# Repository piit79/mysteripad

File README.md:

# Mysteripad

#### WARNING: This project is a work in progress and hasn't been validated yet.

Mysteripad is a through-hole numeric keyboard (or "numpad") matching the form 
factor of the [Mysterium keyboard]((https://github.com/piit79/mysterium)) 
([original](https://github.com/coseyfannitutti/mysterium)), much like the 
[Discipad](https://github.com/piit79/discipad) 
([original](https://github.com/coseyfannitutti/discipad)) matches the 
[Discipline](https://github.com/piit79/discipline) 
([original](https://github.com/coseyfannitutti/discipline)).

Mysteripad was inspired by (but is not based on) the [Discipad](https://github.com/coseyfannitutti/discipad) by Bryan of [cftkb.com](https://cftkb.com/).

## Features

* 17-22 keys, 0-4 rotary encoders (6 rows, 4 columns)
* Hotswappable using Kailh/Gateron hotswap sockets
* All 4 top row positions support either a switch or an EC11 rotary encoder - 4 encoders can be installed at the same time¹
* Optional split 0 support (2x 1u instead of 2u)
* TRRS socket for connection to the next 42. Keebs revision of the Mysterium (V1.5e) via a 4-pin AUX (TRRS) cable (using the I²C bus) so that a single USB cable can be used for both keyboards, similar to split keyboards

¹ To reduce the number of required I/O pins from 8 to 5, any two adjacent encoders share an I/O pin. Therefore, rotating any such encoders at higher speed simultaneously might not work correctly. Other combinations (1-3, 1-4, 2-4) should not be affected.

## Documentation

[Bill of Materials](https://github.com/piit79/mysteripad/tree/main/doc#bill-of-materials)
and [build guide](https://github.com/piit79/mysteripad/tree/main/doc#build-guide) (coming soon)

## Firmware

QMK firmware can be found in [42. Keebs QMK fork](https://github.com/piit79/qmk_firmware/tree/master/keyboards/42keebs/mysteripad).

## Kit availability

You can grab the Gerber zip files from [releases](https://github.com/piit79/mysteripad/releases) 
(coming soon), have the PCBs made at one of the fabs and order all the 
[electronic components](https://github.com/piit79/mysteripad/tree/main/doc#bill-of-materials)
at your favourite electronics store.

A complete kit will also be available from [42. Keebs](https://42keebs.eu/shop/kits/with-discrete-mcu/mysteripad-hotswap-numpad-kit-black-white/) sooner or later (probably in ~~July~~ September 2022).

## TODO

* ~~Add PCB bottom plate~~
* ~~Add PCB switch plate~~
* ~~Add acrylic cover drawing~~
* ~~Create QMK firmware~~
* Add Gerber zip files to releases
* ~~Add BOM~~
* Add build guide

## Revision history

* v1.0 (26/06/2022) - Initial version

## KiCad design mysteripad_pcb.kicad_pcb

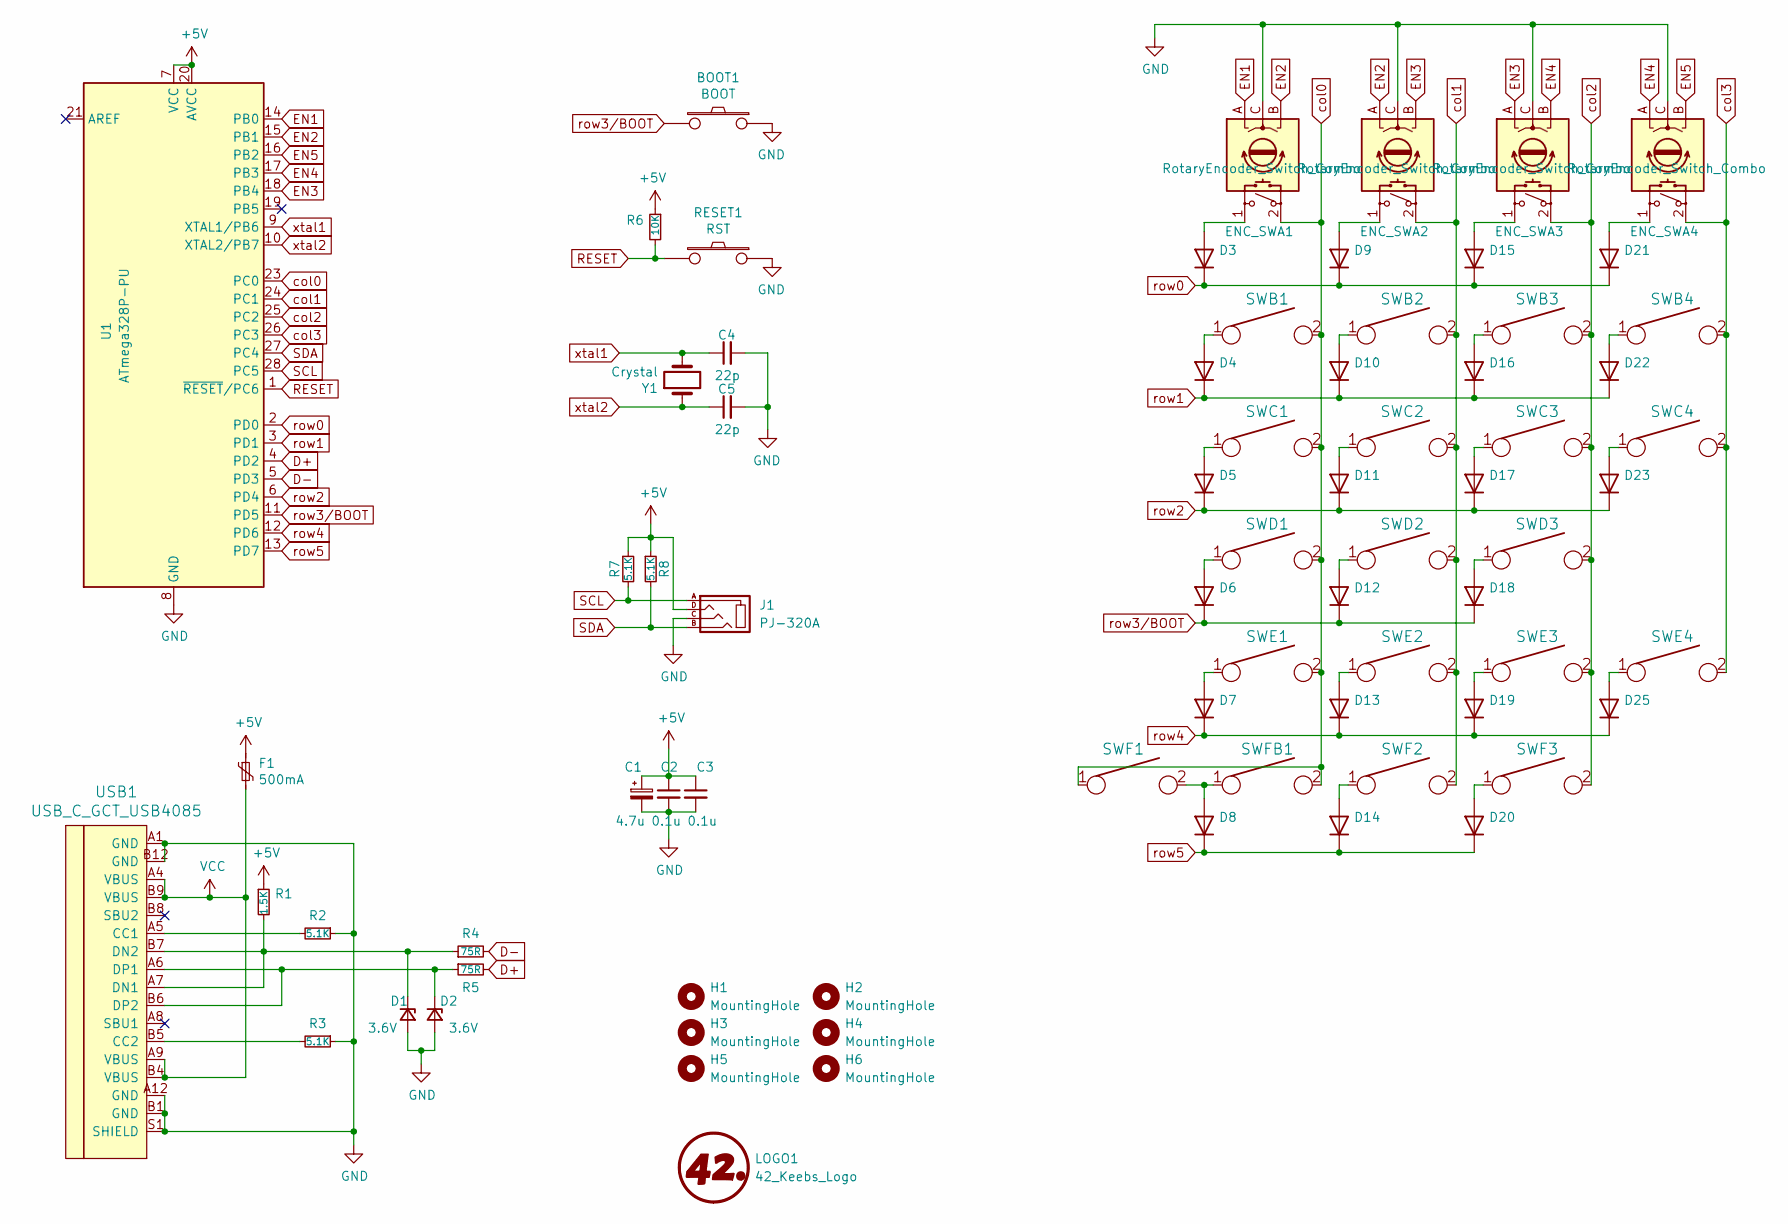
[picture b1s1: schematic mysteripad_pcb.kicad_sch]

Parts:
BOOT1: BOOT; ResetSW_1side
C1: 4.7u; CP_Radial_D4.0mm_P1.50mm
C2, C3: 0.1u; C_Disc_D4.3mm_W1.9mm_P5.00mm
C4, C5: 22p; C_Disc_D3.0mm_W1.6mm_P2.50mm
D1, D2: 3.6V; ZD_DO-35_SOD27_P5.08mm_Horizontal_smaller
D3, D4, D5, D6, D7, D8, D9, D10, D11, D12, D13, D14, D15, D16, D17, D18, D19, D20, D21, D22, D23, D25: D_DO-35_SOD27_P5.08mm_Horizontal
ENC_SWA1, ENC_SWA2, ENC_SWA3, ENC_SWA4: RotaryEncoder_Switch_Combo; Kailh_MX_Socket-plus-EC11-encoder
F1: 500mA; polyfuse_5.1mm
H1, H2, H3, H4, H5, H6: MountingHole; MountingHole_2.2mm_M2_Pad
J1: PJ-320A
LOGO1: 42_Keebs_Logo; 42Keebs-icon-10mm-Mask
R1: 1.5K; R_Axial_DIN0204_L3.6mm_D1.6mm_P5.08mm_Horizontal
R2, R3, R7, R8: 5.1K; R_Axial_DIN0204_L3.6mm_D1.6mm_P5.08mm_Horizontal
R4, R5: 75R; R_Axial_DIN0204_L3.6mm_D1.6mm_P5.08mm_Horizontal
R6: 10K; R_Axial_DIN0204_L3.6mm_D1.6mm_P5.08mm_Horizontal
RESET1: RST; ResetSW_1side
SWB1, SWB2, SWB3, SWB4: KEYSW; Kailh_MX_Socket-swapped-pads
SWC1, SWC2, SWC3: KEYSW; Kailh_MX_Socket-swapped-pads
SWC4: KEYSW; Kailh_MX_Socket-2u-swapped-pads-reversed-stabilizer
SWD1, SWD2, SWD3: KEYSW; Kailh_MX_Socket-swapped-pads
SWE1, SWE2, SWE3: KEYSW; Kailh_MX_Socket-swapped-pads
SWE4: KEYSW; Kailh_MX_Socket-2u-swapped-pads-reversed-stabilizer
SWF1, SWF2, SWF3: KEYSW; Kailh_MX_Socket-swapped-pads
SWFB1: KEYSW; Kailh_MX_Socket-2u-swapped-pads-reversed-stabilizer
U1: ATmega328P-PU; DIP-28_W7.62mm
USB1: USB_C_GCT_USB4085; USB_C_GCT_USB4085-offset-pads
Y1: Crystal; Crystal_HC49-4H_Vertical

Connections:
+5V: C1.1, C2.1, C3.1, F1.1, J1.D, R1.1, R6.1, R7.1, R8.1, U1.7 (VCC), U1.20 (AVCC)
D+: R5.2, U1.4 (PD2)
D-: R4.2, U1.5 (PD3)
EN1: ENC_SWA1.A, U1.14 (PB0)
EN2: ENC_SWA1.B, ENC_SWA2.A, U1.15 (PB1)
EN3: ENC_SWA2.B, ENC_SWA3.A, U1.18 (PB4)
EN4: ENC_SWA3.B, ENC_SWA4.A, U1.17 (PB3)
EN5: ENC_SWA4.B, U1.16 (PB2)
GND: BOOT1.1, C1.2, C2.2, C3.2, C4.2, C5.2, D1.2 (A), D2.2 (A), ENC_SWA1.C, ENC_SWA2.C, ENC_SWA3.C, ENC_SWA4.C, J1.C, R2.1, R3.1, RESET1.1, U1.8 (GND), U1.22 (GND), USB1.A1 (GND), USB1.A12 (GND), USB1.B1 (GND), USB1.B12 (GND), USB1.S1 (SHIELD)
unnamed: D1.1 (K), R1.2, R4.1, USB1.A7 (DN1), USB1.B7 (DN2)
unnamed: D2.1 (K), R5.1, USB1.A6 (DP1), USB1.B6 (DP2)
unnamed: D3.2 (A), ENC_SWA1.1
unnamed: D4.2 (A), SWB1.1
unnamed: D5.2 (A), SWC1.1
unnamed: D6.2 (A), SWD1.1
unnamed: D7.2 (A), SWE1.1
unnamed: D8.2 (A), SWF1.2, SWFB1.1
unnamed: D9.2 (A), ENC_SWA2.1
unnamed: D10.2 (A), SWB2.1
unnamed: D11.2 (A), SWC2.1
unnamed: D12.2 (A), SWD2.1
unnamed: D13.2 (A), SWE2.1
unnamed: D14.2 (A), SWF2.1
unnamed: D15.2 (A), ENC_SWA3.1
unnamed: D16.2 (A), SWB3.1
unnamed: D17.2 (A), SWC3.1
unnamed: D18.2 (A), SWD3.1
unnamed: D19.2 (A), SWE3.1
unnamed: D20.2 (A), SWF3.1
unnamed: D21.2 (A), ENC_SWA4.1
unnamed: D22.2 (A), SWB4.1
unnamed: D23.2 (A), SWC4.1
unnamed: D25.2 (A), SWE4.1
unnamed: R2.2, USB1.A5 (CC1)
unnamed: R3.2, USB1.B5 (CC2)
RESET: R6.2, RESET1.2, U1.1 (~RESET/PC6)
SCL: J1.A, R7.2, U1.28 (PC5)
SDA: J1.B, R8.2, U1.27 (PC4)
VCC: F1.2, USB1.A4 (VBUS), USB1.A9 (VBUS), USB1.B4 (VBUS), USB1.B9 (VBUS)
col0: ENC_SWA1.2, SWB1.2, SWC1.2, SWD1.2, SWE1.2, SWF1.1, SWFB1.2, U1.23 (PC0)
col1: ENC_SWA2.2, SWB2.2, SWC2.2, SWD2.2, SWE2.2, SWF2.2, U1.24 (PC1)
col2: ENC_SWA3.2, SWB3.2, SWC3.2, SWD3.2, SWE3.2, SWF3.2, U1.25 (PC2)
col3: ENC_SWA4.2, SWB4.2, SWC4.2, SWE4.2, U1.26 (PC3)
row0: D3.1 (K), D9.1 (K), D15.1 (K), D21.1 (K), U1.2 (PD0)
row1: D4.1 (K), D10.1 (K), D16.1 (K), D22.1 (K), U1.3 (PD1)
row2: D5.1 (K), D11.1 (K), D17.1 (K), D23.1 (K), U1.6 (PD4)
row3/BOOT: BOOT1.2, D6.1 (K), D12.1 (K), D18.1 (K), U1.11 (PD5)
row4: D7.1 (K), D13.1 (K), D19.1 (K), D25.1 (K), U1.12 (PD6)
row5: D8.1 (K), D14.1 (K), D20.1 (K), U1.13 (PD7)
xtal1: C4.1, U1.9 (XTAL1/PB6), Y1.2
xtal2: C5.1, U1.10 (XTAL2/PB7), Y1.1

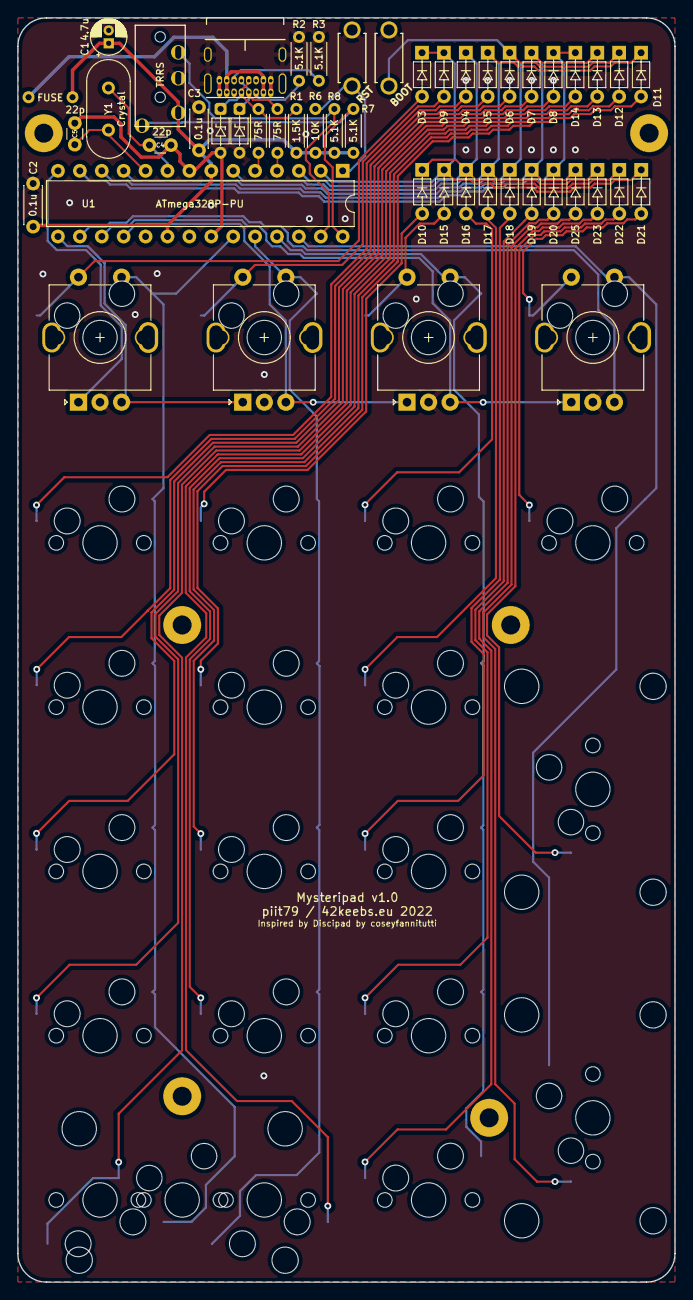
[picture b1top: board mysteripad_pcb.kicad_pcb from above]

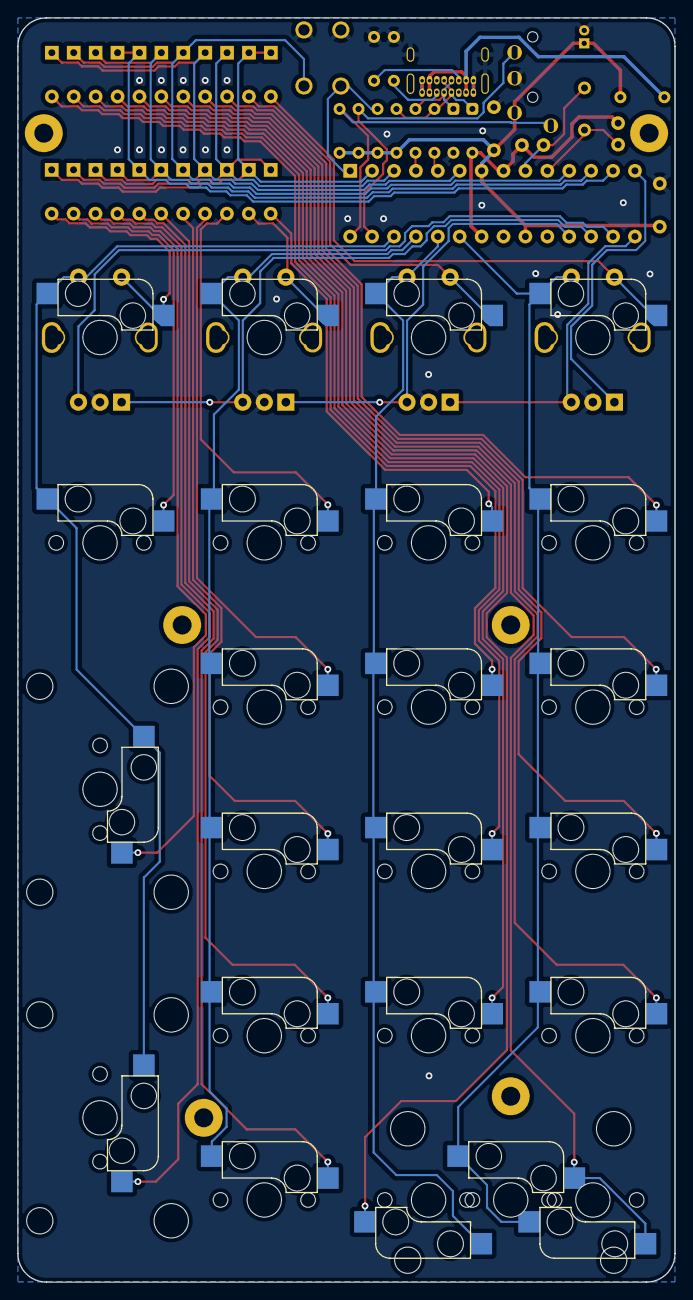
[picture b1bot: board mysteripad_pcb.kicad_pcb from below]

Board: 2 copper layers, 76.2 x 146.6 mm, 74 parts (19 on the bottom side), 51 nets.

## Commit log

2022-06-25 Add kbd KiCad library as submodule
2022-06-25 Add 42. Keebs KiCad library as submodule
2022-06-26 Initial version v1.0 of the PCB
2022-06-27 Add PCB bottom plate
2022-06-27 Add PCB switch plate
2022-06-27 Add acrylic cover drawing
2022-06-27 Add BOM
2022-06-27 Update 42. Keebs lib and update footprints with 3D models
2022-07-10 Clean up/improve routing
2022-07-10 Fix RESET/BOOT silkscreen
2022-07-11 Optimize routing for rounded tracks
2022-07-11 Move MCU and crystal down to avoid fix coutyard overlap
2022-07-11 Update 42. Keebs library
2022-07-11 Finish optimising routing for rounded traces
2022-07-11 Add Gerbers dir to .gitignore
2022-07-11 Add Gerbers dir to .gitignore; update PCB render
2022-08-27 Fix incorrect USB pullup; fix bottom mounting holes
